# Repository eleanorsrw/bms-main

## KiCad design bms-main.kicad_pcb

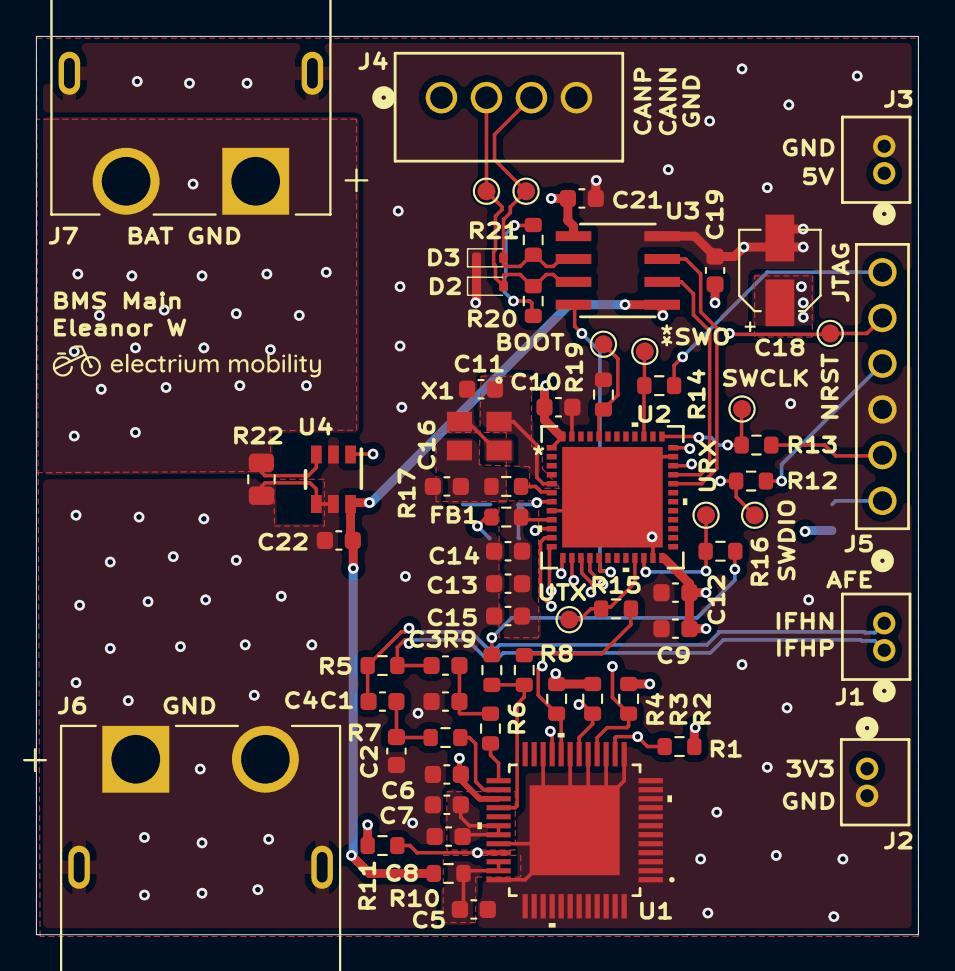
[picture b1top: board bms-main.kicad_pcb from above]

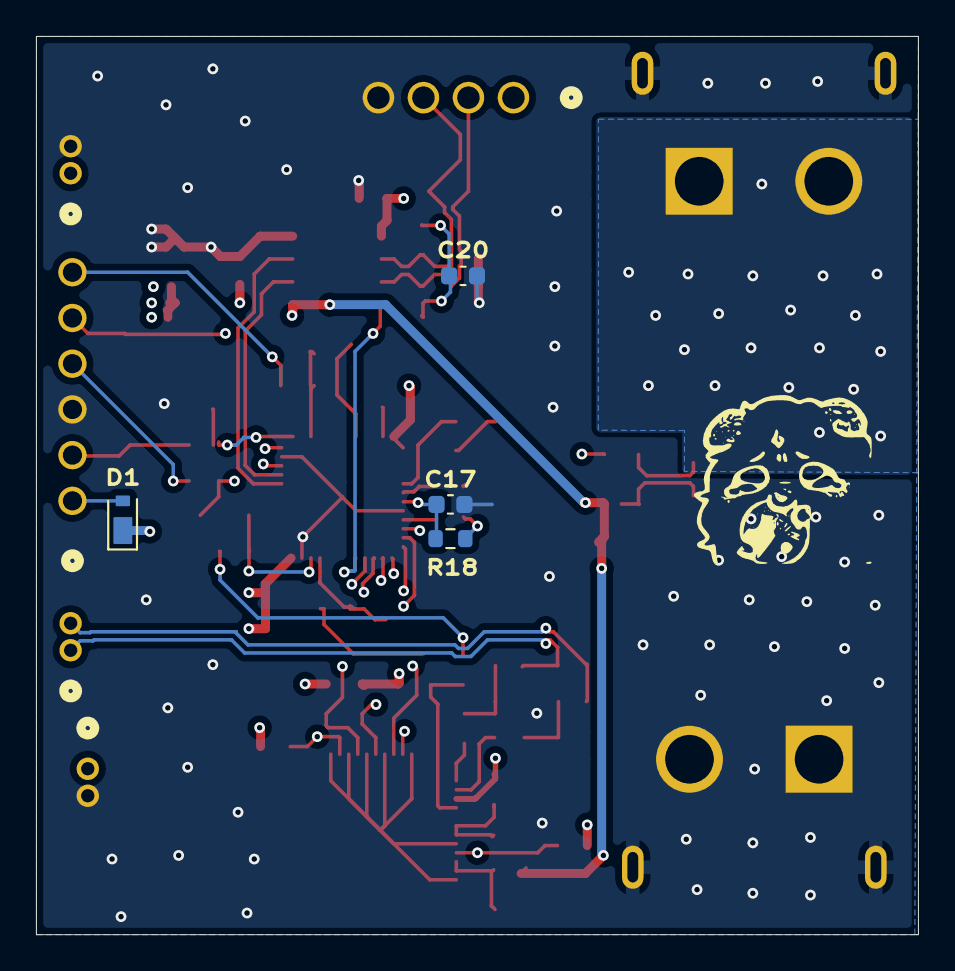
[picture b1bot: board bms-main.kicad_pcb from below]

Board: 4 copper layers, 49.0 x 49.9 mm, 69 parts (4 on the bottom side), 43 nets.

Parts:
BOOT: TestPoint; TestPoint_Pad_D1.0mm
C1, C2: CAP CER 0.22UF 25V X7R 0603; C_0603_1608Metric
C3, C4: CAP CER 0603 1NF 16V X7R 10%; C_0603_1608Metric
C5, C17, C19, C21: CAP CER 0.1UF 25V X7R 0603; C_0603_1608Metric
C6: 0.33uF; C_0603_1608Metric
C7, C8, C10, C12, C15: 0.1uF; C_0603_1608Metric
C9: 4.7uF; C_0603_1608Metric
C11, C16: CAP CER 10PF 50V C0G/NPO 0603; C_0603_1608Metric
C13: 10nF; C_0603_1608Metric
C14: 1uF; C_0603_1608Metric
C18: CAP ALUM 22UF 20% 16V SMD; CP_Wurth_WCAP-ASLI-D4L5.5
C20: CAP CER 0603 4.7NF 16V X7R 10%; C_0603_1608Metric
C22: CAP CER 1UF 16V X7R 0603; C_0603_1608Metric
CANP: TestPoint; TestPoint_Pad_D1.0mm
D1: DIODE SCHOTTKY 30V 1A SOD323F; P39_SOD-323P
D2, D3: TVS DIODE 5VWM 12.5VC SOD-523; P38_SOD-523
FB1: FERRITE BEAD 600 OHM 0603 1LN; R_0603_1608Metric
J1, J2, J3: CONN HEADER VERT 2POS 1.5MM; CONN_B2B-ZR_02P_JST
J4: CONN HEADER VERT 4POS 2.5MM; CONN_B4B-XH-A_JST
J5: PIN HEADER 2.54MM PITCH STR DIP; CONN6x1_G800W302018EU_AMP
J6, J7: XT60PW-M; AMASS_XT60PW-M
N: TestPoint; TestPoint_Pad_D1.0mm
NRST: TestPoint; TestPoint_Pad_D1.0mm
R1, R2, R3, R4, R11, R18: RES SMD 10K OHM 1% 1/8W 0603; R_0603_1608Metric
R5, R8, R19: RES SMD 1K OHM 0.1% 1/10W 0603; R_0603_1608Metric
R6, R7: RES SMD 39 OHM 5% 1/8W 0603; R_0603_1608Metric
R9: RES 0 OHM JUMPER 1/10W 0603; R_0603_1608Metric
R10: RES SMD 5.1 OHM 1% 1/8W 0603; R_0603_1608Metric
R12, R13, R14, R15, R16: RES 100 OHM 1% 1/10W 0603; R_0603_1608Metric
R17: RES 330 OHM 1% 1/10W 0603; R_0603_1608Metric
R20, R21: RES 60.4 OHM 1% 1/10W 0603; R_0603_1608Metric
R22: RES 0.002 OHM 1% 1W 0805; R_0805_2012Metric
SWCLK: TestPoint; TestPoint_Pad_D1.0mm
SWDIO: TestPoint; TestPoint_Pad_D1.0mm
SWO: TestPoint; TestPoint_Pad_D1.0mm
U1: TLE9015DQUXUMA1; PG-TQFP-48-11
U2: STM32L433CCU6; UFQFPN48-7x7mm
U3: IC TRANSCEIVER 1/1 8SO; SOIC8_4P9X3P9MC_MCH
U4: INA181A3IDBVR; DBV0006A_N
URX: TestPoint; TestPoint_Pad_D1.0mm
UTX: TestPoint; TestPoint_Pad_D1.0mm
X1: CRYSTAL 32.0000MHZ 10PF SMD; SMD4_RH100_2P5X3P2-2P2_RAL

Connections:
3V3: C6.1, C9.1, C10.1, C12.1, C21.1, D1.1 (K), FB1.1, J2.1, R1.1, R2.1, R3.1, R4.1, R11.1, R18.1, U1.27 (VDDC), U2.1 (VBAT), U2.24 (VDD), U2.36 (VDDUSB), U2.48 (VDD), U3.5 (VIO)
5V: C18.1, C19.1, C22.1, J3.1, R10.1, U3.1 (TXD), U4.6 (V+)
/CANTranceiver/CAN_N: D3.2 (C), J4.3, N.1 (1_1), R21.2, U3.6 (CANL)
/CANTranceiver/CAN_P: CANP.1 (1_1), D2.2 (C), J4.2, R20.1, U3.7 (CANH)
/CANTranceiver/RXD: U2.32 (PA11), U3.3 (VCC)
/CANTranceiver/STBY: U2.17 (PA7), U3.8 (STBY)
/CANTranceiver/TXD: U2.33 (PA12), U3.2 (GND)
/CurrentSense/C_Sense: U2.10 (PA0), U4.1 (OUT)
/STM/NRST: C17.1, J5.5, NRST.1 (1_1), R18.2, U2.7 (NRST)
/STM/PA5/ERR_loc_OUT: U1.21 (ERR_LOC_OUT), U2.15 (PA5)
/STM/PA6/ERRQ: R11.2, U1.33 (ERRQ), U2.16 (PA6)
/STM/PB10/UART3_TX: R8.2, R15.1
/STM/PB11/UART4_RX: R9.2, R16.1
/STM/PH0-OSC_IN: C11.1, U2.5 (PH0-OSC_IN), X1.1
/STM/PH1-OSC_OUT: R17.1, U2.6 (PH1-OSC_OUT)
/STM/PH3/BOOT0: BOOT.1 (1_1), R19.2, U2.44 (PH3-BOOT0)
/STM/SWCLK: J5.2, R13.1
/STM/SWCLK/PA14: R13.2, SWCLK.1 (1_1), U2.37 (PA14)
/STM/SWDIO: J5.4, R12.1
/STM/SWDIO/PA13: R12.2, SWDIO.1 (1_1), U2.34 (PA13)
/STM/SWO: J5.6, R14.1
/STM/SWO/PB3: R14.2, SWO.1 (1_1), U2.39 (PB3)
/STM/USART4_RX: R16.2, U2.22 (PB11), URX.1 (1_1)
/STM/USART4_TX: R15.2, U2.21 (PB10), UTX.1 (1_1)
/isoUARTTranceiver/ERRQ_EXT: R3.2, U1.18 (ERRQ_EXT), U2.11 (PA1)
/isoUARTTranceiver/ERRQ_RES: R2.2, U1.16 (ERRQ_RES), U2.12 (PA2)
/isoUARTTranceiver/ERR_EXT_OUT: R4.2, U1.20 (ERR_EXT_OUT), U2.14 (PA4)
/isoUARTTranceiver/IFH_Filt_N: R7.1, U1.26 (IFH_L)
/isoUARTTranceiver/IFH_Filt_P: R6.1, U1.25 (LFH_H)
/isoUARTTranceiver/IFH_N: C4.2, J1.2, R5.2
/isoUARTTranceiver/IFH_P: C3.2, J1.1, R5.1
/isoUARTTranceiver/NSLEEP: R1.2, U1.14 (NSLEEP), U2.13 (PA3)
/isoUARTTranceiver/UART_LS: R8.1, R9.1, U1.28 (UART_LS)
GND: C1.2, C2.2, C5.2, C6.2, C7.2, C8.2, C9.2, C10.2, C11.2, C12.2, C13.2, C14.2, C15.2, C16.2, C17.2, C18.2, C19.2, C20.2, C21.2, C22.2, D2.1 (A), D3.1 (A), J2.2, J3.2, J4.4, J5.3, J6.1, J6.2 (N), J6.SH1 (SHIELD), J6.SH2 (SHIELD), J7.SH1 (SHIELD), J7.SH2 (SHIELD), R19.1, R22.2, U1.1 (N.C.), U1.2 (N.C.), U1.3 (N.C.), U1.4 (N.C.), U1.5 (N.C.), U1.6 (N.C.), U1.7 (N.C.), U1.8 (N.C.), U1.9 (N.C.), U1.10 (N.C.), U1.11 (N.C.), U1.12 (N.C.), U1.13 (N.C.), U1.15 (N.C.), U1.17 (N.C.), U1.19 (N.C.), U1.22 (GND), U1.32 (N.C.), U1.36 (N.C.), U1.37 (N.C.), U1.38 (N.C.), U1.39 (N.C.), U1.40 (N.C.), U1.41 (N.C.), U1.42 (N.C.), U1.43 (N.C.), U1.44 (N.C.), U1.45 (N.C.), U1.46 (N.C.), U1.47 (N.C.), U1.48 (N.C.), U1.49 (EPAD), U2.8 (VSSA/VREF-), U2.23 (VSS), U2.35 (VSS), U2.47 (VSS), U2.49 (EPAD), U3.4 (RXD), U4.2 (GND), U4.4 (IN-), U4.5 (REF), X1.2, X1.4
unnamed: C1.1, C3.1, R6.2
unnamed: C2.1, C4.1, R7.2
unnamed: C5.1, R10.2, U1.34 (VS), U1.35 (VS)
unnamed: C16.1, R17.2, X1.3
unnamed: C20.1, R20.2, R21.1
unnamed: D1.2 (A), J5.1
unnamed: C7.1, C8.1, U1.30 (VIO), U1.31 (VREGOUT)
unnamed: C13.1, C14.1, C15.1, FB1.2, U2.9 (VDDA/VREF+)
PD_GND: J7.1, J7.2 (N), R22.1, U4.3 (IN+)

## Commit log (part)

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2026-06-23 schematic
2026-06-25 added stm pins
2026-06-25 finished can and power
2026-06-25 schematic done
2026-06-26 fixed schematic a little
2026-06-26 damir review
2026-06-26 changed stm and stlink
2026-06-28 fixed csense connectors and stm
2026-06-29 tweaked a little
2026-06-29 added passives
2026-06-30 cleaned up schematic
2026-06-30 minor changes
